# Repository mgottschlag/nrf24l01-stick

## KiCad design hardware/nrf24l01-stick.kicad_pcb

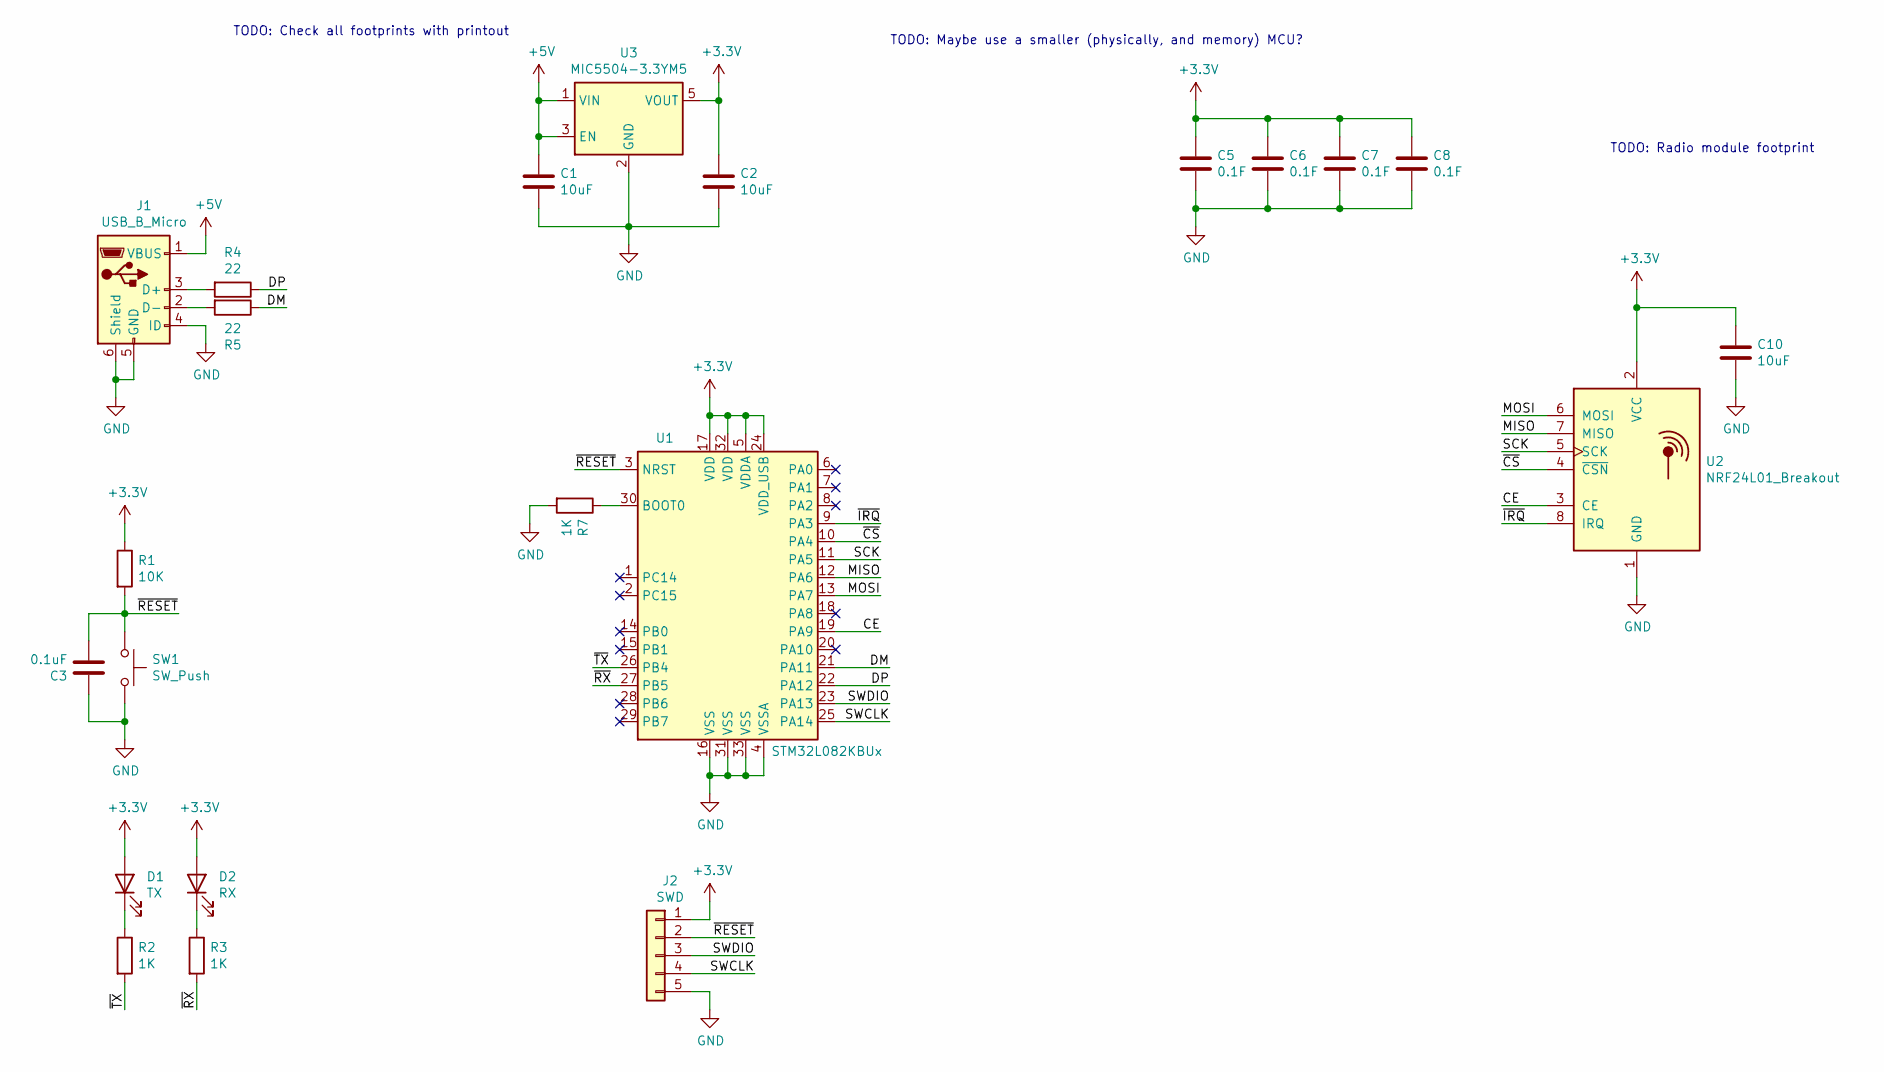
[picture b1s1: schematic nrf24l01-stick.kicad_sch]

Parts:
C1, C2, C10: 10uF; C_0805_2012Metric
C3: 0.1uF; C_0603_1608Metric
C5, C6, C7, C8: 0.1F; C_0603_1608Metric
D1: TX; LED_0603_1608Metric
D2: RX; LED_0603_1608Metric
J1: USB_B_Micro; USB_Micro-B_Amphenol_10104110_Horizontal
J2: SWD; PinHeader_1x05_P2.54mm_Vertical
R1: 10K; R_0603_1608Metric
R2, R3, R7: 1K; R_0603_1608Metric
R4, R5: 22; R_0603_1608Metric
SW1: SW_Push; SW_Push_1P1T_NO_6x6mm_H9.5mm
U1: STM32L082KBUx; QFN-32-1EP_5x5mm_P0.5mm_EP3.45x3.45mm
U2: NRF24L01_Breakout; NRF24L01_PA_Breakout_SMD
U3: MIC5504-3.3YM5; SOT-23-5

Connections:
+3V3: C2.1, C5.1, C6.1, C7.1, C8.1, C10.1, D1.2 (A), D2.2 (A), J2.1, R1.1, U1.5 (VDDA), U1.17 (VDD), U1.24 (VDD_USB), U1.32 (VDD), U2.2 (VCC), U3.5 (VOUT)
+5V: C1.1, J1.1 (VBUS), U3.1 (VIN), U3.3 (EN)
/CE: U1.19 (PA9), U2.3 (CE)
/DM: R5.1, U1.21 (PA11)
/DP: R4.1, U1.22 (PA12)
/MISO: U1.12 (PA6), U2.7 (MISO)
/MOSI: U1.13 (PA7), U2.6 (MOSI)
/SCK: U1.11 (PA5), U2.5 (SCK)
/SWCLK: J2.4, U1.25 (PA14)
/SWDIO: J2.3, U1.23 (PA13)
/~CS: U1.10 (PA4), U2.4 (~CSN)
/~IRQ: U1.9 (PA3), U2.8 (IRQ)
/~RESET: C3.2, J2.2, R1.2, SW1.1, U1.3 (NRST)
/~RX: R3.2, U1.27 (PB5)
/~TX: R2.2, U1.26 (PB4)
GND: C1.2, C2.2, C3.1, C5.2, C6.2, C7.2, C8.2, C10.2, J1.4 (ID), J1.5 (GND), J1.6 (Shield), J2.5, R7.2, SW1.2, U1.4 (VSSA), U1.16 (VSS), U1.31 (VSS), U1.33 (VSS), U2.1 (GND), U3.2 (GND)
unnamed: D1.1 (K), R2.1
unnamed: D2.1 (K), R3.1
unnamed: J1.2 (D-), R5.2
unnamed: J1.3 (D+), R4.2
unnamed: R7.1, U1.30 (BOOT0)
no_connect_(U1-Pad1): U1.1 (PC14)
no_connect_(U1-Pad2): U1.2 (PC15)
no_connect_(U1-Pad6): U1.6 (PA0)
no_connect_(U1-Pad7): U1.7 (PA1)
no_connect_(U1-Pad8): U1.8 (PA2)
no_connect_(U1-Pad14): U1.14 (PB0)
no_connect_(U1-Pad15): U1.15 (PB1)
no_connect_(U1-Pad18): U1.18 (PA8)
no_connect_(U1-Pad20): U1.20 (PA10)
no_connect_(U1-Pad28): U1.28 (PB6)
no_connect_(U1-Pad29): U1.29 (PB7)
no_connect_(U3-Pad4): U3.4 (NC)

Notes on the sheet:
TODO: Check all footprints with printout
TODO: Maybe use a smaller (physically, and memory) MCU?
TODO: Radio module footprint

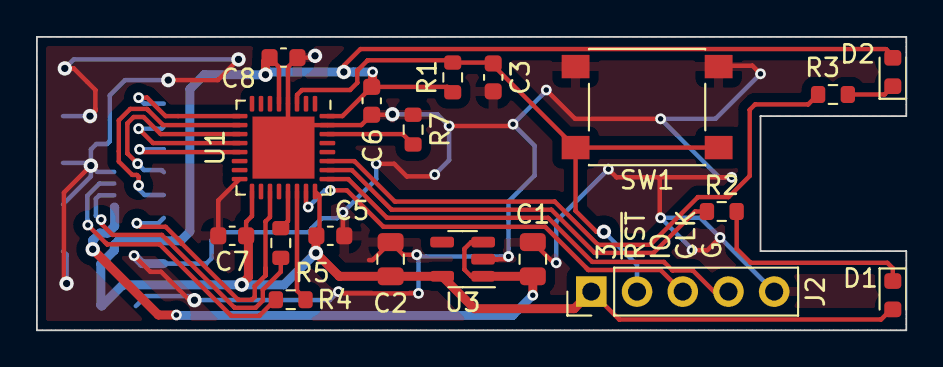
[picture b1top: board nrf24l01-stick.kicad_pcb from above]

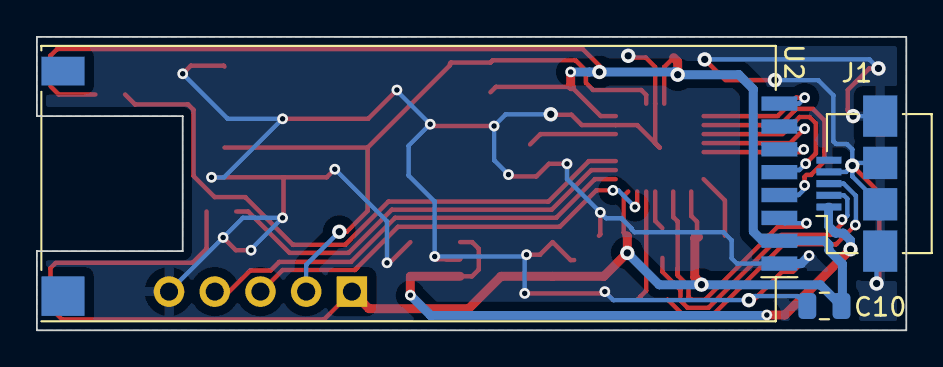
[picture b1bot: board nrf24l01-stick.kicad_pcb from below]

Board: 2 copper layers, 48.3 x 16.3 mm, 22 parts (3 on the bottom side), 21 nets.

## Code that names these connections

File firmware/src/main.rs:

//! Firmware for the NRF24L01 stick.
#![no_main]
#![no_std]

use panic_semihosting as _;
use stm32l0xx_hal::exti::Exti;
use stm32l0xx_hal::prelude::*;
use stm32l0xx_hal::rcc;
use stm32l0xx_hal::syscfg::SYSCFG;
use stm32l0xx_hal::usb::{UsbBus, UsbBusType, USB};
use usb_device::bus::UsbBusAllocator;
use usb_device::prelude::*;

use adapter::Adapter;

mod adapter;
mod buffer;

#[rtic::app(device = stm32l0xx_hal::pac, peripherals = true)]
const APP: () = {
    struct Resources {
        usb_dev: UsbDevice<'static, UsbBusType>,
        serial: usbd_serial::SerialPort<'static, UsbBusType>,
        adapter: Adapter,
    }

    #[init]
    fn init(ctx: init::Context) -> init::LateResources {
        static mut USB_BUS: Option<UsbBusAllocator<UsbBusType>> = None;

        let mut rcc = ctx.device.RCC.freeze(rcc::Config::hsi16());
        let mut syscfg = SYSCFG::new(ctx.device.SYSCFG, &mut rcc);
        let hsi48 = rcc.enable_hsi48(&mut syscfg, ctx.device.CRS);
        let mut exti = Exti::new(ctx.device.EXTI);

        let gpioa = ctx.device.GPIOA.split(&mut rcc);
        let gpiob = ctx.device.GPIOB.split(&mut rcc);

        let tx_led = gpiob.pb4.into_push_pull_output();
        let rx_led = gpiob.pb5.into_push_pull_output();

        let usb = USB::new(ctx.device.USB, gpioa.pa11, gpioa.pa12, hsi48);

        *USB_BUS = Some(UsbBus::new(usb));

        let serial = usbd_serial::SerialPort::new(USB_BUS.as_ref().unwrap());

        // This PID/VID combination is selected from the pid.codes PID space and only intended for
        // software development. It is not universally unique and should not be used outside of
        // test environments!
        let usb_dev = UsbDeviceBuilder::new(USB_BUS.as_ref().unwrap(), UsbVidPid(0x1209, 0x000d))
            .manufacturer("Mathias Gottschlag")
            .product("nrf24l01-stick")
            .serial_number("TEST")
            .device_class(usbd_serial::USB_CLASS_CDC)
            .build();

        let radio_irq = gpioa.pa3.into_pull_up_input();
        let radio_cs = gpioa.pa4.into_push_pull_output();
        let radio_ce = gpioa.pa9.into_push_pull_output();
        let radio_sck = gpioa.pa5;
        let radio_miso = gpioa.pa6;
        let radio_mosi = gpioa.pa7;
        let adapter = Adapter::new(
            ctx.device.SPI1,
            radio_irq,
            radio_cs,
            radio_ce,
            radio_sck,
            radio_miso,
            radio_mosi,
            tx_led.downgrade(),
            rx_led.downgrade(),
            &mut rcc,
            &mut exti,
            &mut syscfg,
        );

        init::LateResources {
            usb_dev,
            serial,
            adapter,
        }
    }

    #[task(binds = EXTI2_3, resources = [usb_dev, serial, adapter])]
    fn radio_irq(mut ctx: radio_irq::Context) {
        ctx.resources.adapter.poll_radio();
        // We might have to send packets to the host.
        ctx.resources
            .adapter
            .send_usb_serial(&mut ctx.resources.serial);
        usb_poll(
            &mut ctx.resources.usb_dev,
            &mut ctx.resources.serial,
            ctx.resources.adapter,
        );
    }

    #[task(binds = USB, resources = [usb_dev, serial, adapter])]
    fn usb(mut ctx: usb::Context) {
        usb_poll(
            &mut ctx.resources.usb_dev,
            &mut ctx.resources.serial,
            ctx.resources.adapter,
        );
    }
};

fn usb_poll(
    usb_dev: &mut UsbDevice<'static, UsbBusType>,
    serial: &mut usbd_serial::SerialPort<'static, UsbBusType>,
    adapter: &mut Adapter,
) {
    usb_dev.poll(&mut [serial]);

    let mut buf = [0u8; 64];
    while let Ok(count) = serial.read(&mut buf) {
        adapter.data_from_serial(&buf[0..count]);
    }
    adapter.send_usb_serial(serial);
    // TODO: Do we have to poll again after a serial write?
    usb_dev.poll(&mut [serial]);
}

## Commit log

2020-10-14 Initial import (including a dummy USB driver).
2020-10-14 Fix manufacturer/product info and add an udev rule file.
2020-10-15 Linux driver API example.
2020-10-16 firmware: Modified to support the bluepill board.
2020-10-16 Add Cargo.lock of the libraries to .gitignore.
2020-10-16 Some more driver and protocol code.
2020-10-17 More driver implementation and serial device protocol.
2020-10-17 protocol: Add postcard serialization/deserialization.
2020-10-17 driver: Add tokio codec for packet interface.
2020-10-18 driver: Implemented sending/receiving data via the serial port.
2020-10-18 Improve protocol and driver API to reduce delay between RX/TX.
2020-10-18 driver: Fix out-of-bounds access.
2020-10-18 firmware: Fix compiling with recent toolchain, LTO, debug symbols, rustfmt.
2020-10-18 firmware: openocd stlink-v2-1.cfg is deprecated.
2020-10-18 firmware: Switch to interrupt-based usb.
2020-10-18 firmware: Initialize NRF24L01 module.
2020-10-24 firmware: NRF24L01 EXTI interrupt setup.
2020-10-24 firmware: Forward data received via usb serial to the adapter type.
2020-10-24 driver: Serialize length-1, not length, to eliminate one corner case.
    Packets must never be empty.
2020-10-24 firmware: Split data from the USB serial interface into packets.
2020-10-24 firmware: Functions to send USB packets back to the host.
2021-01-13 Port firmware to STM32F429 and add more packet processing code.
2021-01-13 firmware: Implement proper responses and reset.
2021-01-15 Implement receiving packets.
    Sending does not seem to work yet.
2021-01-15 driver: Remove debug spam and compiler warnings, fix crash in the example.
2021-01-15 firmware: Use patched NRF24L01 driver.
2021-01-15 firmware: Test FIFO state before sending.
2021-01-21 Add NRF24L01+PA SMD kicad footprint.
2021-01-21 Add first parts of the PCB.
2021-01-22 Designed the rest of the PCB.
2021-01-23 Add labels for the SWD pinout.
2021-03-19 Ignore firmware workspace target directory.
2021-03-19 Port the firmware to the proper target hardware.
    Interrupt-based USB is still missing.
2021-03-19 firmware: Poll from USB and GPIO interrupts instead of the idle task.
2022-01-24 Add support for receiving of ACK payloads.
2022-01-27 [driver] Set packet length to size of actual content
2022-01-27 [driver] Do not set tty to exclusive use on macos
2022-01-27 Fix mut
2022-01-27 [driver] Allow setting tty as a parameter
2024-03-18 Update Tokio to version '1'
2024-03-19 Fix updating tokio on linux
